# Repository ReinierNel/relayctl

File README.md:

# relayctl -- TBA

## Install

Write [Raspberry Pi OS Lite](https://downloads.raspberrypi.org/raspios_lite_armhf/images/raspios_lite_armhf-2022-04-07/2022-04-04-raspios-bullseye-armhf-lite.img.xz) to micro SD card, insert and boot the Pi

Set your your time zone using `sudo raspi-config` and any other preferences you might have.

Next install using the following command

```bash
curl https://raw.githubusercontent.com/ReinierNel/relayctl/1.0.0/setup.sh | bash
```

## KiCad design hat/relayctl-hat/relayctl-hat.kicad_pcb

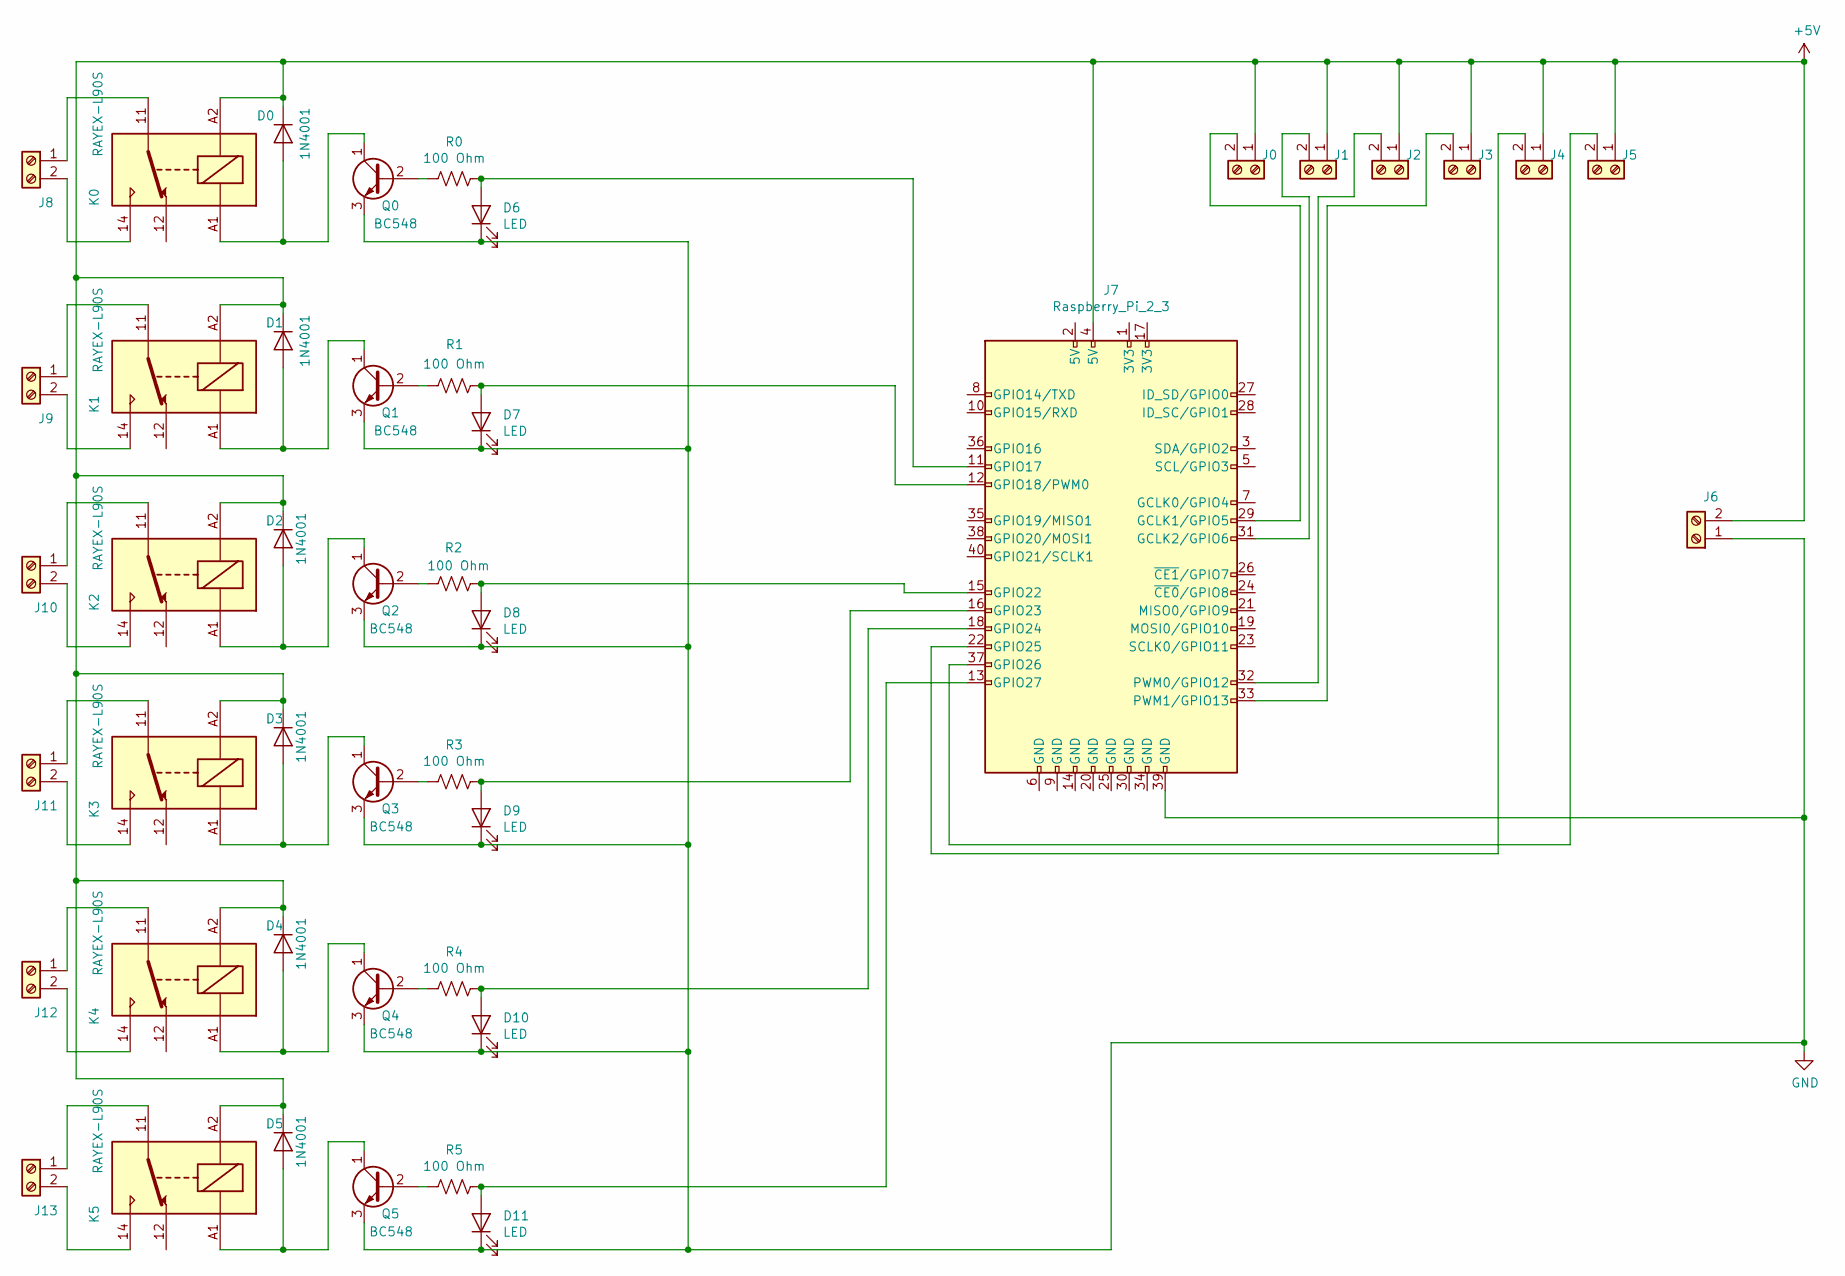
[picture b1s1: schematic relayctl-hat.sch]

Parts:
D0, D1, D2, D3, D4, D5: 1N4001; D_DO-41_SOD81_P10.16mm_Horizontal
D6, D7, D8, D9, D10, D11: LED; LED_D3.0mm
J0, J1, J2, J3, J4, J5: Screw_Terminal_01x02; TerminalBlock_Altech_AK300-2_P5.00mm
J6, J8, J9, J10, J11, J12, J13: Screw_Terminal_01x02; TerminalBlock_RND_205-00241_1x02_P10.16mm_Horizontal
J7: Raspberry_Pi_2_3; PinHeader_2x20_P2.00mm_Vertical
K0, K1, K2, K3, K4, K5: RAYEX-L90S; Relay_SPDT_RAYEX-L90S
Q0, Q1, Q2, Q3, Q4, Q5: BC548; TO-92_Inline
R0, R1, R2, R3, R4, R5: 100 Ohm; R_Axial_DIN0414_L11.9mm_D4.5mm_P15.24mm_Horizontal

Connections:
+5V: D0.1 (K), D1.1 (K), D2.1 (K), D3.1 (K), D4.1 (K), D5.1 (K), J0.1, J1.1, J2.1, J3.1, J4.1, J5.1, J6.2, J7.4 (5V), K0.A2, K1.A2, K2.A2, K3.A2, K4.A2, K5.A2
GND: D6.1 (K), D7.1 (K), D8.1 (K), D9.1 (K), D10.1 (K), D11.1 (K), J6.1, J7.39 (GND), Q0.3 (E), Q1.3 (E), Q2.3 (E), Q3.3 (E), Q4.3 (E), Q5.3 (E)
unnamed: D0.2 (A), K0.A1, Q0.1 (C)
unnamed: D1.2 (A), K1.A1, Q1.1 (C)
unnamed: D2.2 (A), K2.A1, Q2.1 (C)
unnamed: D3.2 (A), K3.A1, Q3.1 (C)
unnamed: D4.2 (A), K4.A1, Q4.1 (C)
unnamed: D5.2 (A), K5.A1, Q5.1 (C)
unnamed: D6.2 (A), J7.11 (GPIO17), R0.2
unnamed: D7.2 (A), J7.12 (GPIO18/PWM0), R1.2
unnamed: D8.2 (A), J7.15 (GPIO22), R2.2
unnamed: D9.2 (A), J7.16 (GPIO23), R3.2
unnamed: D10.2 (A), J7.18 (GPIO24), R4.2
unnamed: D11.2 (A), J7.13 (GPIO27), R5.2
unnamed: J0.2, J7.29 (GCLK1/GPIO5)
unnamed: J1.2, J7.31 (GCLK2/GPIO6)
unnamed: J2.2, J7.32 (PWM0/GPIO12)
unnamed: J3.2, J7.33 (PWM1/GPIO13)
unnamed: J4.2, J7.22 (GPIO25)
unnamed: J5.2, J7.37 (GPIO26)
unnamed: J8.1, K0.11
unnamed: J8.2, K0.14
unnamed: J9.1, K1.11
unnamed: J9.2, K1.14
unnamed: J10.1, K2.11
unnamed: J10.2, K2.14
unnamed: J11.1, K3.11
unnamed: J11.2, K3.14
unnamed: J12.1, K4.11
unnamed: J12.2, K4.14
unnamed: J13.1, K5.11
unnamed: J13.2, K5.14
unnamed: Q0.2 (B), R0.1
unnamed: Q1.2 (B), R1.1
unnamed: Q2.2 (B), R2.1
unnamed: Q3.2 (B), R3.1
unnamed: Q4.2 (B), R4.1
unnamed: Q5.2 (B), R5.1

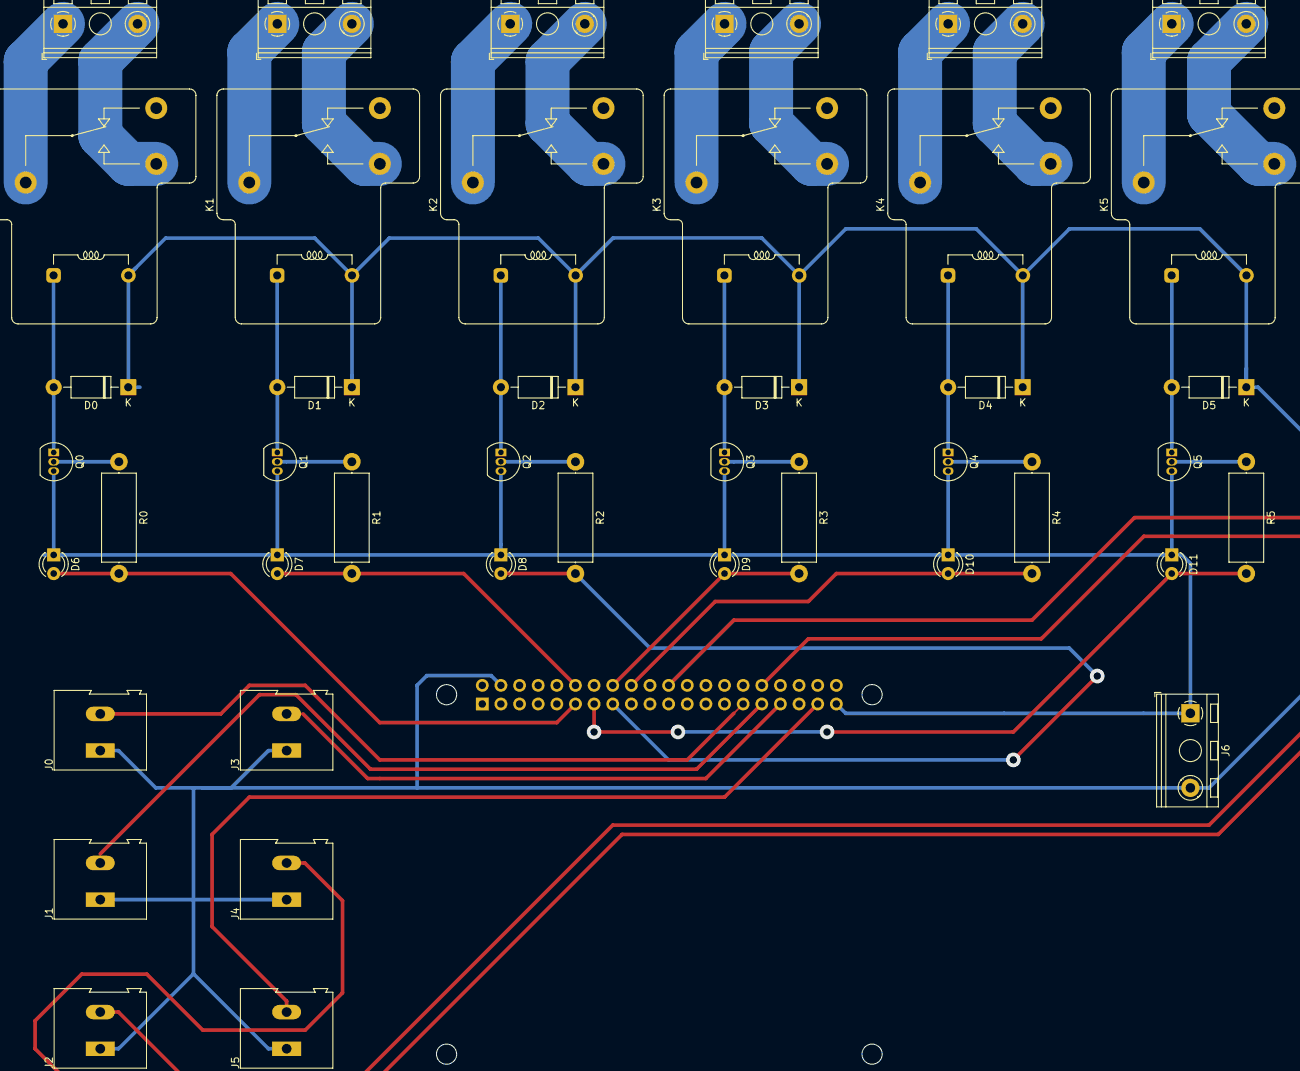
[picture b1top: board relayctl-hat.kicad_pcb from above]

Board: 2 copper layers, 44 parts (0 on the bottom side), 38 nets.

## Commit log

2021-12-28 work in progress
    script not done yet! do not use!!!
2021-12-28 work in progress
    will complete the readme once setup.sh is done
2021-12-29 updated install dir to /etc/relayctl
    /home/pi might not be present in some instances, also added Parimiterisation of relays and scheduler_frequency
2021-12-29 added basic install script
    not spellchecked and will need refinement but should work fine.
2021-12-29 added basic install instructions
    will add more details later
2022-01-04 added external switches and updated setup
2022-01-04 fix README
2022-01-04 added exnternal.sh to rc.local setup section
2022-01-04 updated readme with manual install instructions
2022-01-04 added check to enable/disable logging
2022-01-04 fix: logging to file instead of stout and file
2022-01-09 started building basic crud api
2022-01-10 improved logging and simplified schedule
2022-01-11 added api script and shellcheck fixes to main scripts
2022-01-11 updated setup to test api install on fresh pi
2022-01-11 fix typo
2022-01-11 fix name
2022-01-11 Update default
2022-01-11 updated nginx and api.cgi
2022-01-12 updated json output
2022-01-12 added metadat filter on logging
2022-01-12 added new setting
2022-01-12 updated logging json output
2022-01-12 fixed list file prems
2022-01-13 added shcedules and swiches end poits
    not complete but functional still need validation on post / delete requists
2022-01-13 removed unused endpoits
2022-01-13 added tests, api-key reset script and fixed buxs
2022-01-13 Update issue templates
2022-01-14 added basic wire frame
2022-01-17 added testing scripts for setup and api also added dockerfiles
2022-01-17 fixed yes to all install
2022-01-18 refactored setup to include web ui and small optimizations
2022-01-18 fixed script flags
2022-01-18 fix setup script args
2022-01-18 removed testing sections for debugging
2022-01-18 testing html
2022-01-19 finalized bas webui
2022-01-20 updated web ui
2022-01-21 added testing resouces
2022-01-21 testing acctions for deploy
2022-01-21 try exporting env vars
2022-01-21 check az cli installed
2022-01-21 try using azure cli
2022-01-21 try using azure cli fixed secrets
2022-01-21 try exporing arm secrets
2022-01-21 added env var export step
2022-01-21 split env vars into azure and ssh
2022-01-21 try sending var to file
2022-01-21 try using heredoc
2022-01-21 try using heredoc fixed spaces
2022-01-21 removed unused export and added line brake to end
2022-01-21 try using cat with stdin
2022-01-21 try using echo
2022-01-21 try making export and terraform one line
2022-01-21 removed braking quotes
2022-01-21 echo out all file based vars
2022-01-21 removed unused tf vars
2022-01-21 fixed Reference to undeclared resource
2022-01-21 fixed file name Invalid function argument
2022-01-21 fixed added features blocks
2022-01-21 fixed plan file path
2022-01-21 added terraform apply
2022-01-21 added terraform destroy
2022-01-21 try using needs statment on destroy step
2022-01-21 try working out current derectory on destroy job
2022-01-21 try adding artifacts
2022-01-21 using ssh key artifacts
2022-01-21 removed artifacts added ssh key export
2022-01-21 try running test agains API
2022-01-21 fixed command
2022-01-21 removed unused job
2022-01-21 conencting to vm via ssh
2022-01-21 try and find ip address file
2022-01-21 try and install openssh-client
2022-01-21 try and install openssh-client and running multiple commands at onec
2022-01-21 removed array on run
2022-01-21 add .ssh folder
2022-01-21 -o StrictHostKeyChecking no
2022-01-21 added executable flag to script
2022-01-21 updated test script
2022-01-21 updated setup script and schipt executioner in tf also added allow destroy to run if test fails
2022-01-21 try adding verbosity to test
2022-01-21 fixed json output on switch/delete 422 responce
2022-01-21 added shellcheck job
2022-01-21 update testing actions
2022-01-21 fix path to shellcheck api file
2022-01-21 try and fix regex issue SC2076
2022-01-21 Fixed missing programs jq and curl
2022-01-21 Fixed requirments on cleanup job
2022-01-21 try fix regex issue on /relays/0 <-- regex a number
2022-01-21 try fix regex issue
2022-01-21 removed if from cleanup
2022-01-24 fix branch selector on install testing and added self singed certs to installer still need testing
2022-01-24 fix terraform apply on actions
2022-01-24 fix small issue with ssl certs
2022-01-25 fix cert issue dest
2022-01-25 fixed nginx config and updated test to use ssl
2022-01-25 fix for cleanup job
2022-01-25 added input validation
2022-01-25 fixed api test script and added validation check for output on api
2022-01-25 updated tests, api and actions
2022-01-25 fixed bug validation var was set after return resulting in a no var set
2022-01-25 added demo scedules and switchs mapping
2022-01-25 swicthed post and delete around with get tests
2022-01-28 added basics for pem auth
2022-01-30 fixed protocol on API calles
2022-01-31 changes api key header
2022-01-31 fixed tests and moved apy key to APIKEY header
2022-01-31 fix broken endpoint updated setup
2022-02-01 added base64 encoding for cookie and added setting to allow per user logging
2022-02-01 updated api key checks on web-ui
2022-02-04 bug fix and deply on cleanup
2022-02-04 added sleep for 600 seconds before destroy
2022-02-04 want eks cool
2022-02-04 fixed pipeline
2022-02-04 added testing brach where CI will live
2022-02-04 fix yaml indent issue on actions workflow
2022-02-10 added listenr for api to control relays
2022-02-10 fixed output json
2022-02-25 updatded pcb
2022-02-25 added gbr and drl files
2022-04-06 rebuilding using better techstack
2022-04-12 added fastapi + typer cli
2022-04-13 Updatd cli
2022-04-13 updated reamde
2022-04-21 added js functions to manage relays on webui
2022-04-21 added web ui for switches
2022-04-21 added schedule web ui
2022-04-21 done js curd functions
2022-04-23 added deamon
2022-04-23 updated deamone
2022-04-24 added setup script still need to test
2022-04-24 dockerized api
2022-04-24 fixed small install issues
2022-04-24 fixed path to start script
2022-04-24 start script on setup
2022-04-24 fix api start script
2022-04-24 added terraform example and added some notes
